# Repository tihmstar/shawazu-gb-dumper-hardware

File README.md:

# Shawazu GB Dumper Hardware
Custom Shawazu PCB for dumping GB / GBC / GBA games and savegames.  
This is an easy to solder DIY project.

# 3D printed case
A 3d printed case is available for rev 3 / rev 4 boards [here](https://github.com/tihmstar/shawazu-gb-dumper-hardware/tree/master/case).  
**Note: The case does not fit rev2 boards!**

# Voltage switch 
GB / GBC cartridges run on 5V.  
GBA cartridges run on 3.3V.  

Always set the correct voltage **before** plugging in the cartridge!

# Bill Of Materials
* 1 x Raspberry Pi Pico
* 7 x BOB-12009 (4 bit level shifter)
* 1 x Switch (3 pin 2 position panel, 3mm)
* 1 x 32pin Gameboy Cartridge Connector
* 2 x wires

It is important that the pico has the footprint of an original pico. It is possible to use cheap USB-C picos from china but original is recommended.  
The project uses GPIO23 as a bidirectional data pin, which on a raspberry pi pico is connected to the on-board SMPS Power Save pin. While doing this is kinda out of spec, it works fine in practise. However, on some cheap USB-C picos from china it can cause bootloops and thus may be problematic. It worked fine for me most of the time, but a few picos had the bootloop issue.

The switches i used are https://www.amazon.de/gp/product/B09TVFF6KW. They fit like 95%. Just a little squeezing is needed.  

For the connector, just pick one from AliExpress. They should be pretty much all the same, so any that looks like it fits should work.

# Assembly

A video tutorial on how to assembly the board is available here:  

In General:  
1) **Flash and test the pico!!!!!**
2) Solder the 7 level shifter
3) Solder the connector
4) Solder the switch
5) Solder the pico (front side only)
6) **Test the pico again!!!**
7) Solder to the pico testpoint through the whole in the back of the PCB
8) **Test the pico again!!!**
9) Optional 1: Solder the TP near the switch on the PCB to the LED of the Pico (check video)
10) **Test the pico again!!!**
11) Optional 2: (check video)
- Remove the two resistors on the pico
- **Test the pico again!!!**
- Solder the upper pad of the resistor placeholder on the PCB to the correct pad where you removed the resistors on the pico (check video)
12) Finally: test the finished assembly

**Make sure to test the pico over and over during assembly! Otherwise it will be extremely difficult to debug what is wrong in case the final thing doesn't _just work_!!!!**  

### "Testing the pico"
Flash the [Shawazu firmware](https://github.com/tihmstar/shawazu-gb-dumper) to your pico and make sure a drive called _SHAWAZU_ appears when you plug it in. The drive should contain one file _Info.txt_ which says that no cartridge is connected. After the relevant assembly steps connect the pico again and check if the drive with the file still shows up.  
If the drive doesn't show up before assembly and you realize the pico is dead, do no solder it on the PCB.  
**Once soldered to the PCB it is ~~impossible~~ extremely diffucult to remove the pico without damaging anything!!!**  
If the drive showed up before assembly but does no longer show up after a certain step, go back and debug/fix your previous assembly step. If you don't test the pico after every modification it will be very hard to tell which step exactly causes the failure!

# Optional solders
There are 2 so called "optional solders" on the board. You will need to solder both correctly if you want to have all features of shawazu. Let's take a look at what each of them do

## Optional solder 1
This solder point refers to the testpoint which is closer to the power switch on the PCB. The TP needs to be soldered to GPIO25, which is used by the LED. The LED seems not to interfere and can be left on the board.  
There are multiple revisions of the PCB with different pinout.

### Optional solder: PICO_<span style="text-decoration:overline">CS</span>
**You pretty much always want to solder this!**

The negated chipselect line is set low (enabled) when talking to GB / GBC ROM and set high (disabled) when talking to GB / GBC SRAM. Some cartridges (especially those without savestate) may ignore this so those can be talked to without this. It is possible to enable the solderbridge to ground this pin to always have the ROM enabled, but this may cause issues in some GB / GBC games.

On GBA games this line is used to "clock" the bus for transfer to ROM (and flash/eeprom savestate).   
**Without this line GBA cartridges will not work**.

### Optional solder: PICO_CLK
**Needed for Gameboy Camera. Other Cartridges may work without this**  

The gameboy CLK line is rarely used by any GB / GBC cartridge. The only cartridge i have tested that actually needs this line is the Gameboy Camera. If you don't plan on using the Gameboy Camera it is fine to leave this alone. Do NOT ground this line with the solderbridge.

As far as i'm aware, GBA does not use the CLK.

## Optional solder 2
This solder point refers the the upper pad of the resistor placeholder. Rev 4 has a dedicated TP on on the PCB labled as "<span style="text-decoration:overline">CS2</span>", which is connected to the upper pad of the resistor placeholder. Earlier revisions do not have a dedicated TP, there you just solder to the upper resistor placeholder. 
This point should be connected to GPIO24 on the pico. That GPIO is normally used to detect whether 5V (eg via USB) is available, or if the pico is powered by 3.3V. To use the GPIO is is **required** to remove 2 resistors.   
**Without removing the two resistors you cannot use the GPIO!!!!** 

### Optional solder: <span style="text-decoration:overline">CS2</span>
**Solder for GBA savegame support. If you don't care about GBA, place a 10k resistor on the PCB**

On GB / GBC cartridges this pin is called _<span style="text-decoration:overline">RST</span>_ and used to reset the Gameboy CPU from the cartridge. Most cartridges do not care about this pin, but some (Gameboy Camera) want this to be pulled high.

On GBA this pin is called <span style="text-decoration:overline">CS2</span> and is used to "clock" the SRAM. Without this pin SRAM is not accessible and thus savegame of some GBA cartridges cannot be read / written. Some cartridges which use EEPROM / Flash based savegame may not need this pin, but if you plan to use GBA cartridges it is recommended to solder this.

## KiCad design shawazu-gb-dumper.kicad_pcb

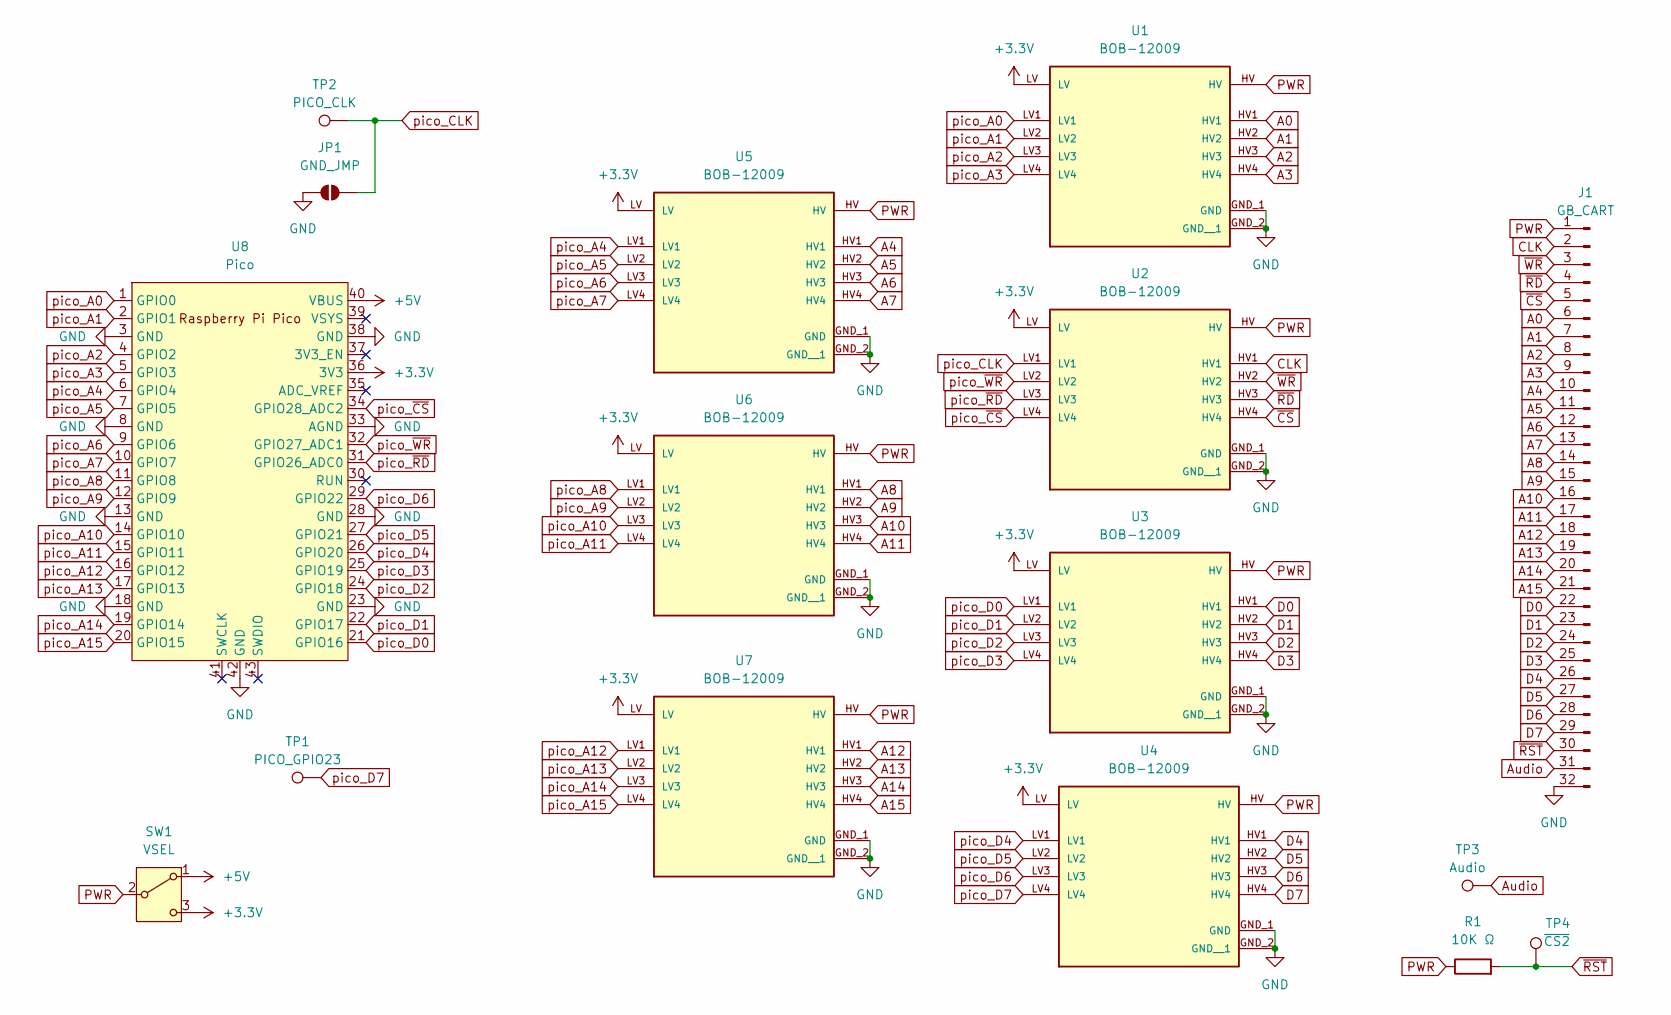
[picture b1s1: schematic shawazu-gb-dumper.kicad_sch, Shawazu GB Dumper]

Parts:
J1: GB_CART; GB_CART_4holes
JP1: GND_JMP; SolderJumper-2_P1.3mm_Open_RoundedPad1.0x1.5mm
R1: 10K Ω; R_Axial_DIN0309_L9.0mm_D3.2mm_P12.70mm_Horizontal
SW1: VSEL; SW_Slide_SPDT_Straight_CK_OS102011MS2Q
TP1: PICO_GPIO23; TestPoint_Plated_Hole_D4.0mm
TP2: PICO_CLK; TestPoint_Pad_D2.0mm
TP3: Audio; TestPoint_Pad_D2.0mm
TP4: ~{CS2}; TestPoint_Pad_D2.0mm
U1, U2, U3, U4, U5, U6, U7: BOB-12009; CONV_BOB-12009; PARTREV 01
U8: Pico; RPi_Pico_SMD_TH

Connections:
+3.3V: SW1.3 (C), U1.LV, U2.LV, U3.LV, U4.LV, U5.LV, U6.LV, U7.LV, U8.36 (3V3)
+5V: SW1.1 (A), U8.40 (VBUS)
A0: J1.6, U1.HV1
A1: J1.7, U1.HV2
A2: J1.8, U1.HV3
A3: J1.9, U1.HV4
A4: J1.10, U5.HV1
A5: J1.11, U5.HV2
A6: J1.12, U5.HV3
A7: J1.13, U5.HV4
A8: J1.14, U6.HV1
A9: J1.15, U6.HV2
A10: J1.16, U6.HV3
A11: J1.17, U6.HV4
A12: J1.18, U7.HV1
A13: J1.19, U7.HV2
A14: J1.20, U7.HV3
A15: J1.21, U7.HV4
Audio: J1.31, TP3.1
CLK: J1.2, U2.HV1
D0: J1.22, U3.HV1
D1: J1.23, U3.HV2
D2: J1.24, U3.HV3
D3: J1.25, U3.HV4
D4: J1.26, U4.HV1
D5: J1.27, U4.HV2
D6: J1.28, U4.HV3
D7: J1.29, U4.HV4
GND: J1.32, JP1.1 (A), U1.GND_1 (GND), U1.GND_2 (GND__1), U2.GND_1 (GND), U2.GND_2 (GND__1), U3.GND_1 (GND), U3.GND_2 (GND__1), U4.GND_1 (GND), U4.GND_2 (GND__1), U5.GND_1 (GND), U5.GND_2 (GND__1), U6.GND_1 (GND), U6.GND_2 (GND__1), U7.GND_1 (GND), U7.GND_2 (GND__1), U8.3 (GND), U8.8 (GND), U8.13 (GND), U8.18 (GND), U8.23 (GND), U8.28 (GND), U8.33 (AGND), U8.38 (GND), U8.42 (GND)
PWR: J1.1, R1.1, SW1.2 (B), U1.HV, U2.HV, U3.HV, U4.HV, U5.HV, U6.HV, U7.HV; also elsewhere on the board
pico_A0: U1.LV1, U8.1 (GPIO0)
pico_A1: U1.LV2, U8.2 (GPIO1)
pico_A2: U1.LV3, U8.4 (GPIO2)
pico_A3: U1.LV4, U8.5 (GPIO3)
pico_A4: U5.LV1, U8.6 (GPIO4)
pico_A5: U5.LV2, U8.7 (GPIO5)
pico_A6: U5.LV3, U8.9 (GPIO6)
pico_A7: U5.LV4, U8.10 (GPIO7)
pico_A8: U6.LV1, U8.11 (GPIO8)
pico_A9: U6.LV2, U8.12 (GPIO9)
pico_A10: U6.LV3, U8.14 (GPIO10)
pico_A11: U6.LV4, U8.15 (GPIO11)
pico_A12: U7.LV1, U8.16 (GPIO12)
pico_A13: U7.LV2, U8.17 (GPIO13)
pico_A14: U7.LV3, U8.19 (GPIO14)
pico_A15: U7.LV4, U8.20 (GPIO15)
pico_CLK: JP1.2 (B), TP2.1, U2.LV1
pico_D0: U3.LV1, U8.21 (GPIO16)
pico_D1: U3.LV2, U8.22 (GPIO17)
pico_D2: U3.LV3, U8.24 (GPIO18)
pico_D3: U3.LV4, U8.25 (GPIO19)
pico_D4: U4.LV1, U8.26 (GPIO20)
pico_D5: U4.LV2, U8.27 (GPIO21)
pico_D6: U4.LV3, U8.29 (GPIO22)
pico_D7: TP1.1, U4.LV4
pico_~CS: U2.LV4, U8.34 (GPIO28_ADC2)
pico_~RD: U2.LV3, U8.31 (GPIO26_ADC0)
pico_~WR: U2.LV2, U8.32 (GPIO27_ADC1)
~CS: J1.5, U2.HV4
~RD: J1.4, U2.HV3
~RST: J1.30, R1.2, TP4.1; also elsewhere on the board
~WR: J1.3, U2.HV2

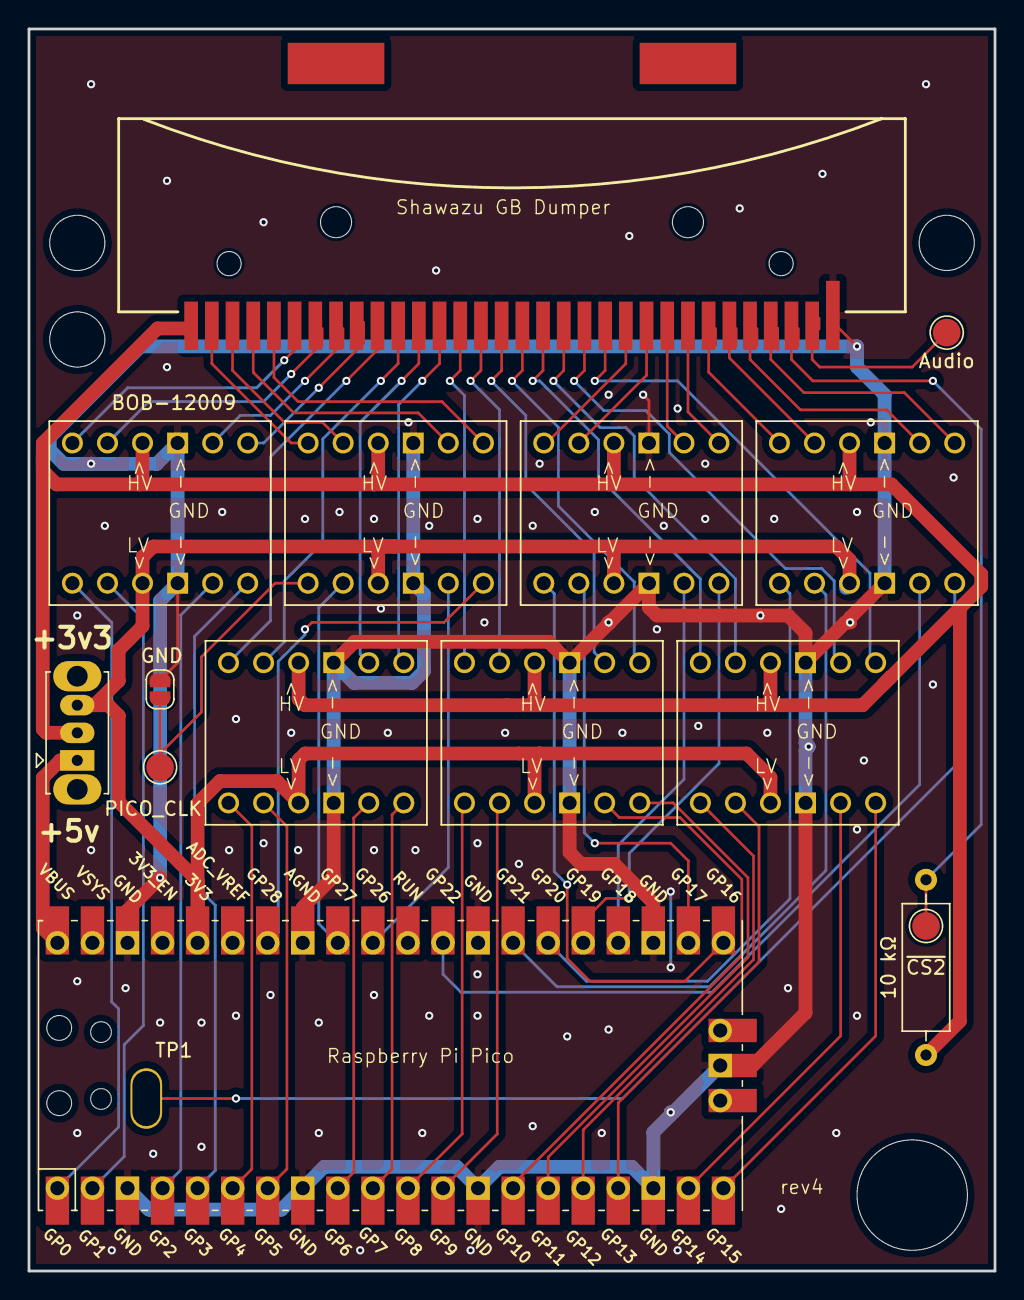
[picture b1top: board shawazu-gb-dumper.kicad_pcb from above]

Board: 2 copper layers, 70.0 x 90.0 mm, 16 parts (0 on the bottom side), 62 nets.

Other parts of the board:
10 kΩ: 10K Ω; R_Axial_DIN0309_L9.0mm_D3.2mm_P12.70mm_Horizontal

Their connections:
PWR: 10 kΩ.1; also elsewhere on the board
~RST: 10 kΩ.2; also elsewhere on the board

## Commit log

2024-03-28 new hardware design
2024-03-29 Fell for: Trap for young players
2024-04-02 switched TP nCS with CLK
2024-04-02 removed from gnd plate
2024-04-02 improve gnd
2024-04-03 move repos
2024-04-03 new PCB release
2024-04-03 pcb v2 (actually)
2024-04-03 add more vias because vias are free (this on i actually ordered)
2024-04-15 rev4
2024-04-21 add 3D printable case (for rev3/rev4 boards)
2024-04-21 case v4
2024-06-16 add readme
2024-06-16 add images
2024-06-16 update readme with images
2024-06-16 fix video
2024-06-16 add 3d case images
